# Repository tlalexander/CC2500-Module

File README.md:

CC2500 thing
===========================

This is a module for the CC2500 wireless chip from TI, made in Eagle. Though modules are already available, I was unable to find any that were open source, which was annoying, so I made one for you to have and play with.

It uses a folded dipole antenna, because that's way easier to lay out (and I don't know anything about wireless). For more info see TI CC2500 Design Note DN004, which, if you're lucky, might be at http://www.ti.com/lit/an/swra118/swra118.pdf.

You may have noticed the part where I mention I don't know anything about wireless (aside from the fact that Jesus used it to fool the Mayans into believing he'd turned water into slightly older water). Well, since I don't know anything about wireless, this may totally not work. I think it will, but unfortunately it's literally impossible to ever find out.

Feel free to fork this and add changes as necessary. I'll license this with the horribly named Creative Commons Attribution-ShareAlike 3.0 Unported License. Which means, more or less, tell people you got it from me, and if you distribute it, use the same license.
http://creativecommons.org/licenses/by-sa/3.0/deed.en_US

That said, if you do actually sell these, I wouldn't *mind* a kickback. But I won't require one, because that's annoying.

CC2500 footprint came from https://github.com/chiengineer/Eagle-Libraries/blob/master/Wireless/chipcon-ti.lbr though I modified it significantly.

Library used here is now https://github.com/tlalexander/Taylors-Eagle-Library, and also probably some parts from Sparkfun.

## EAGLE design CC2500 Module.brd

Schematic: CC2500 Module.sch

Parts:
C1: C-USC1206; C1206
C_P17, C_P18, C_P19: 18p; 0603-CAP
C_RF1, C_RF2, C_RF3, C_RF4, C_RF5: 0.1u; 0603-CAP
JP1: M081X08; 1X08
LED1: LED1206; LED-1206
R4: 56k; 0402-RES
R13: 330R; 0402-RES
U$22: ANTENNA_DIPOLE; CC2500_FOLDED_DIPOLE_ANTENNA
U$23: 7A-26.000MAAJ-T; 5X3.2MM_SMD_XTAL

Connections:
+3V3: C1.1, C_RF1.2, C_RF2.2, C_RF3.2, C_RF4.2, C_RF5.2, JP1.2, LED1.A; also elsewhere on the board
DCOUPL: C_P19.2; also elsewhere on the board
GND: C1.2, C_P17.1, C_P18.1, C_P19.1, C_RF1.1, C_RF2.1, C_RF3.1, C_RF4.1, C_RF5.1, JP1.1, R4.2, R13.2; also elsewhere on the board
MISO: JP1.6; also elsewhere on the board
MOSI: JP1.8; also elsewhere on the board
unnamed: LED1.C, R13.1
unnamed 7: U$22.P$1; also elsewhere on the board
unnamed 8: U$22.P$2; also elsewhere on the board
unnamed 9: C_P17.2, U$23.X2; also elsewhere on the board
unnamed 10: C_P18.2, U$23.X1; also elsewhere on the board
unnamed 11: R4.1; also elsewhere on the board
RF_CS: JP1.3; also elsewhere on the board
RF_GDO0: JP1.4; also elsewhere on the board
RF_GDO2: JP1.5; also elsewhere on the board
SPCK: JP1.7; also elsewhere on the board

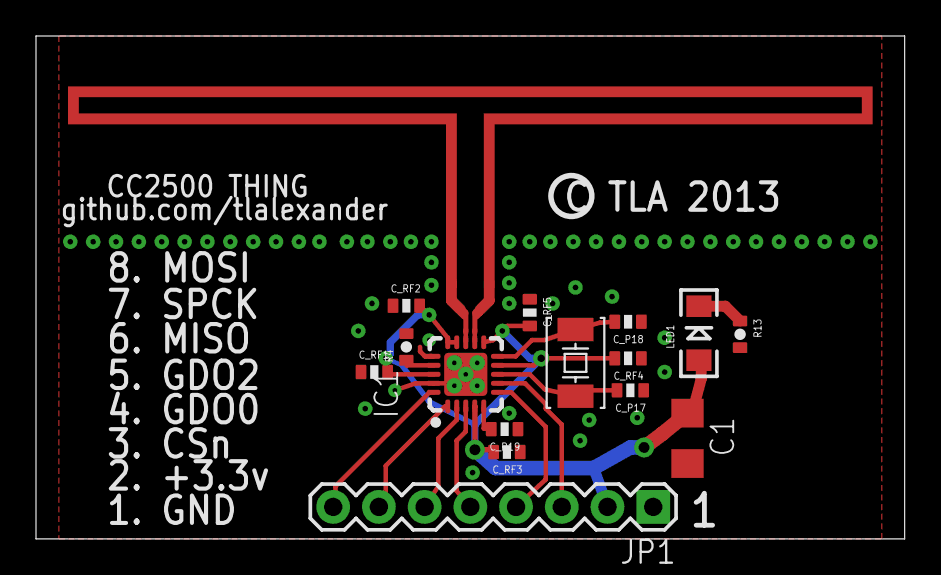
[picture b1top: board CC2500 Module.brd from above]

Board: 2 copper layers, 48.3 x 27.9 mm, 16 parts (0 on the bottom side), 15 nets.

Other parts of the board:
IC1: CC2500; QLP-20

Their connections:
+3V3: IC1.4, IC1.9, IC1.11, IC1.14, IC1.15, IC1.18; also elsewhere on the board
DCOUPL: IC1.5; also elsewhere on the board
GND: IC1.16, IC1.19, IC1.PAD, IC1.THERMAL1, IC1.THERMAL2, IC1.THERMAL3, IC1.THERMAL4, IC1.THERMAL5; also elsewhere on the board
MISO: IC1.2; also elsewhere on the board
MOSI: IC1.20; also elsewhere on the board
unnamed 7: IC1.12; also elsewhere on the board
unnamed 8: IC1.13; also elsewhere on the board
unnamed 9: IC1.8; also elsewhere on the board
unnamed 10: IC1.10; also elsewhere on the board
unnamed 11: IC1.17; also elsewhere on the board
RF_CS: IC1.7; also elsewhere on the board
RF_GDO0: IC1.6; also elsewhere on the board
RF_GDO2: IC1.3; also elsewhere on the board
SPCK: IC1.1; also elsewhere on the board

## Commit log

2012-12-28 Added Readme
2012-12-30 Added Gerber Files
